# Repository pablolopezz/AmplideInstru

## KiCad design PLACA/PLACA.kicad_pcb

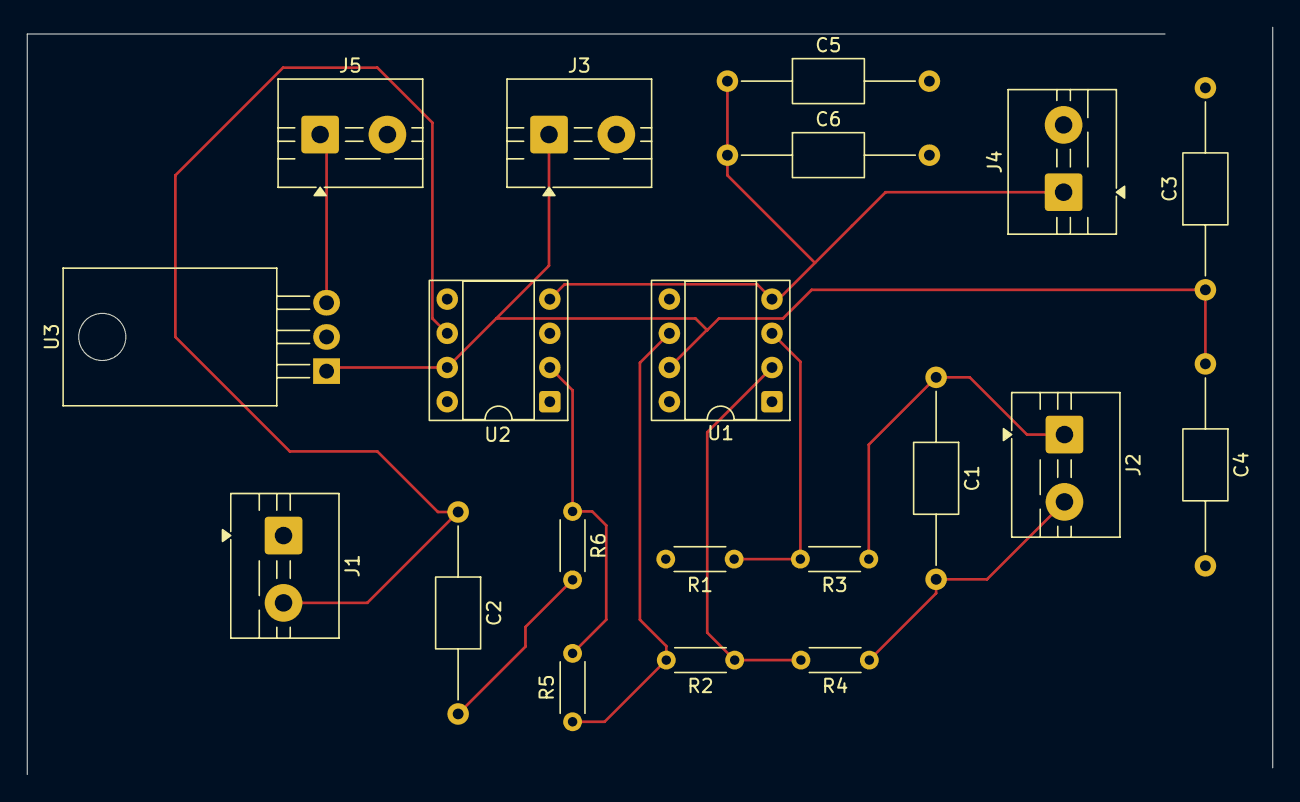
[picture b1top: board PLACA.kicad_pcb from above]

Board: 2 copper layers, 92.5 x 55.5 mm, 20 parts (0 on the bottom side), 12 nets.

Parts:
C1, C2, C3, C4, C5, C6: C; C_Axial_L5.1mm_D3.1mm_P15.00mm_Horizontal
J1, J2, J3, J4, J5: Screw_Terminal_01x02; TerminalBlock_MaiXu_MX126-5.0-02P_1x02_P5.00mm
R1, R2, R3, R4, R5, R6: R; R_Axial_DIN0204_L3.6mm_D1.6mm_P5.08mm_Horizontal
U1, U2: LM741; DIP-8_W7.62mm_Socket
U3: LM7805_TO220; TO-220-3_Horizontal_TabDown

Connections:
GND: C3.2, C4.2, C5.2, C6.2, J1.1, J3.2, J4.2, J5.2, R1.2, U2.3 (+), U3.2 (GND)
unnamed: C2.2, R6.2
unnamed: C2.1, J1.2, U2.6
unnamed: C1.1, J2.1, R3.1
unnamed: C1.2, J2.2, R4.1
unnamed: C3.1, C4.1, J3.1, U1.7 (V+), U2.7 (V+), U3.1 (VI)
unnamed: C5.1, C6.1, J4.1, U1.4 (V-), U2.4 (V-)
unnamed: J5.1, U3.3 (VO)
unnamed: R2.2, R5.1, U1.6
unnamed: R1.1, R3.2, U1.3 (+)
unnamed: R2.1, R4.2, U1.2 (-)
unnamed: R5.2, R6.1, U2.2 (-)

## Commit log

2025-10-14 lo que llevamos
2025-10-14 Retoques
2025-10-15 Datos finales y esquemático ideal
2025-10-15 Cambios en kicad
2025-10-15 Esquematico con implementacion del LM741
